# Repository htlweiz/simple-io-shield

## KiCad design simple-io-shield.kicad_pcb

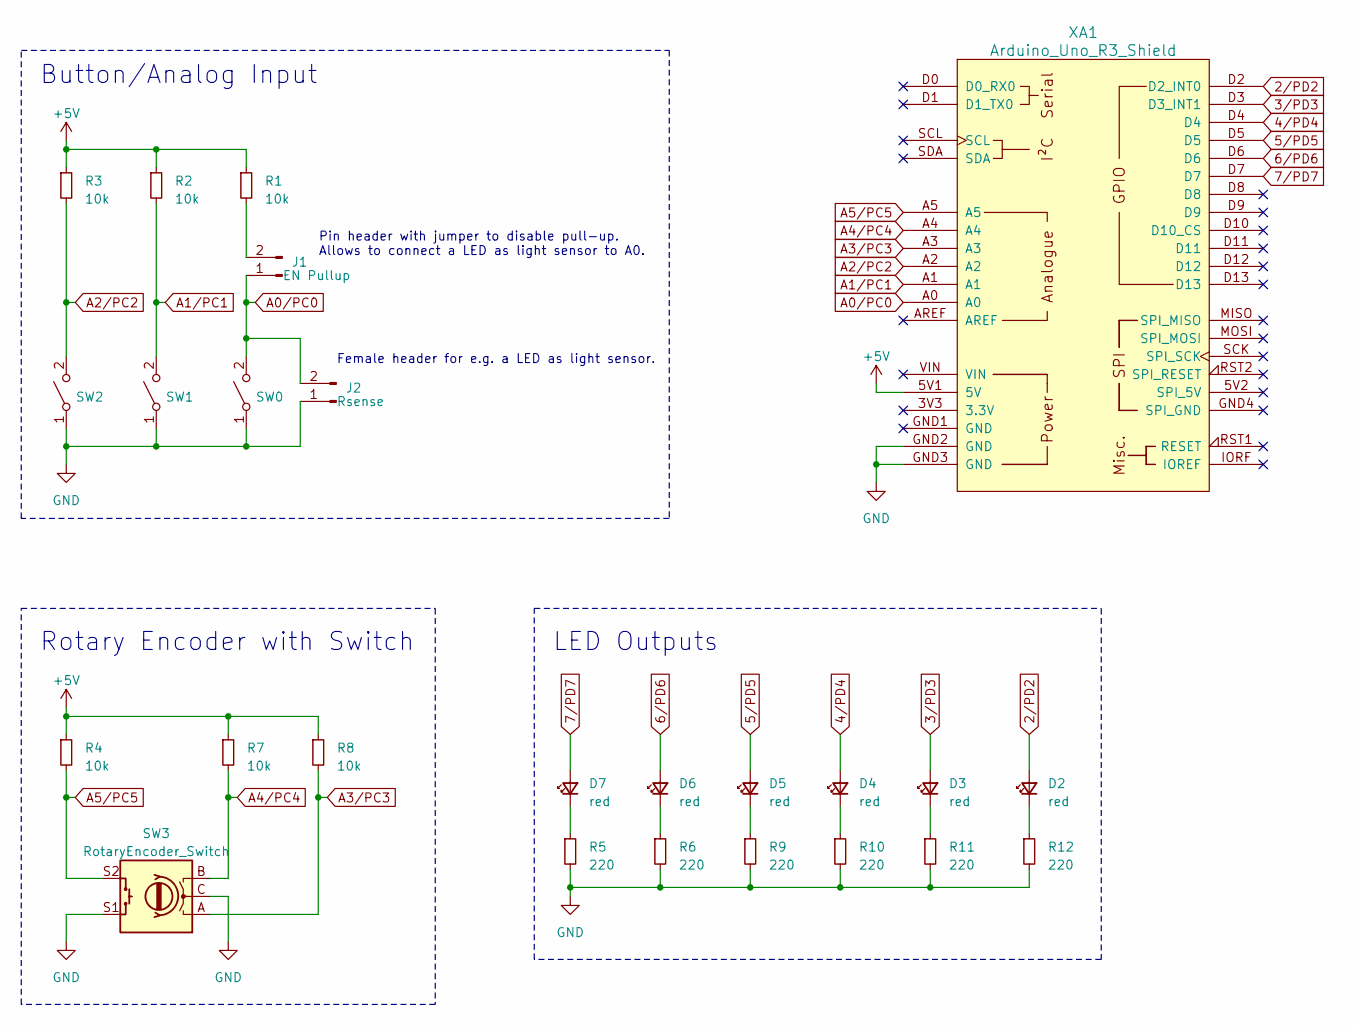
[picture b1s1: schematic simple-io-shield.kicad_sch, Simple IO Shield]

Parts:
D2, D3, D4, D5, D6, D7: red; LED_0603_1608Metric
J1: Conn_01x02_Pin; PinHeader_2x01_P2.54mm_Vertical
J2: Conn_01x02_Pin; PinSocket_2x01_P2.54mm_Vertical
R1, R2, R3, R4, R7, R8: 10k; R_0402_1005Metric
R5, R6, R9, R10, R11, R12: 220; R_0402_1005Metric
SW0, SW1, SW2: SW_SPST; SW_SPST_TS-1187A
SW3: RotaryEncoder_Switch; RotaryEncoder_Alps_EC11E-Switch_Vertical_H20mm
XA1: Arduino_Uno_R3_Shield

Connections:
2/PD2: D2.2 (A), XA1.D2 (D2_INT0)
3/PD3: D3.2 (A), XA1.D3 (D3_INT1)
4/PD4: D4.2 (A), XA1.D4
5/PD5: D5.2 (A), XA1.D5
6/PD6: D6.2 (A), XA1.D6
7/PD7: D7.2 (A), XA1.D7
+5V: R1.1, R2.1, R3.1, R4.1, R7.1, R8.1, XA1.5V1 (5V)
A0/PC0: J1.1, J2.2, SW0.2 (B), XA1.A0
A1/PC1: R2.2, SW1.2 (B), XA1.A1
A2/PC2: R3.2, SW2.2 (B), XA1.A2
A3/PC3: R8.2, SW3.A, XA1.A3
A4/PC4: R7.2, SW3.B, XA1.A4
A5/PC5: R4.2, SW3.S2, XA1.A5
GND: J2.1, R5.2, R6.2, R9.2, R10.2, R11.2, R12.2, SW0.1 (A), SW1.1 (A), SW2.1 (A), SW3.C, SW3.S1, XA1.GND2 (GND), XA1.GND3 (GND)
unnamed: D2.1 (K), R12.1
unnamed: D3.1 (K), R11.1
unnamed: D4.1 (K), R10.1
unnamed: D5.1 (K), R9.1
unnamed: D6.1 (K), R6.1
unnamed: D7.1 (K), R5.1
unnamed: J1.2, R1.2

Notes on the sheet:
LED Outputs
Female header for e.g. a LED as light sensor.
Button/Analog Input
Rotary Encoder with Switch
Pin header with jumper to disable pull-up. Allows to connect a LED as light sensor to A0.

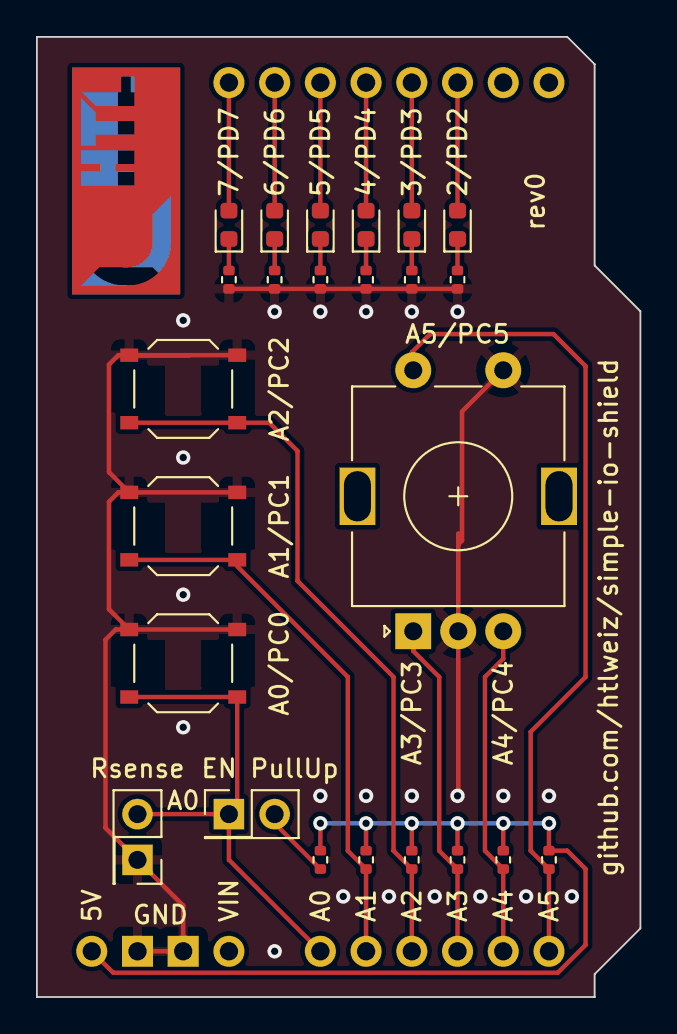
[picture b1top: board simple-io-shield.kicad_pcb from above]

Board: 2 copper layers, 33.5 x 53.3 mm, 25 parts (0 on the bottom side), 21 nets.

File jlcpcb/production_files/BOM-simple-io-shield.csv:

Comment,Designator,Footprint,LCSC
red,"D2,D3,D4,D5,D6,D7",LED_0603_1608Metric,C2286
220,"R10,R11,R12,R5,R6,R9",R_0402_1005Metric,C25091
10k,"R1,R2,R3,R4,R7,R8",R_0402_1005Metric,C25744
SW_SPST,"SW0,SW1,SW2",SW_SPST_TS-1187A,C318884
Arduino_Uno_R3_Shield,XA1,Arduino_Uno_R3_Shield,
Conn_01x02_Pin,J2,PinSocket_2x01_P2.54mm_Vertical,
RotaryEncoder_Switch,SW3,RotaryEncoder_Alps_EC11E-Switch_Vertical_H20mm,
Conn_01x02_Pin,J1,PinHeader_2x01_P2.54mm_Vertical,

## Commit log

2023-03-08 initial commit, rev0
2023-03-08 removed holes outside board edge
2023-03-17 added arduino pin name to Rsense
